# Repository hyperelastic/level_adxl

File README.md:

# level_adxl
Electronic level using the adxl325 accelerometer

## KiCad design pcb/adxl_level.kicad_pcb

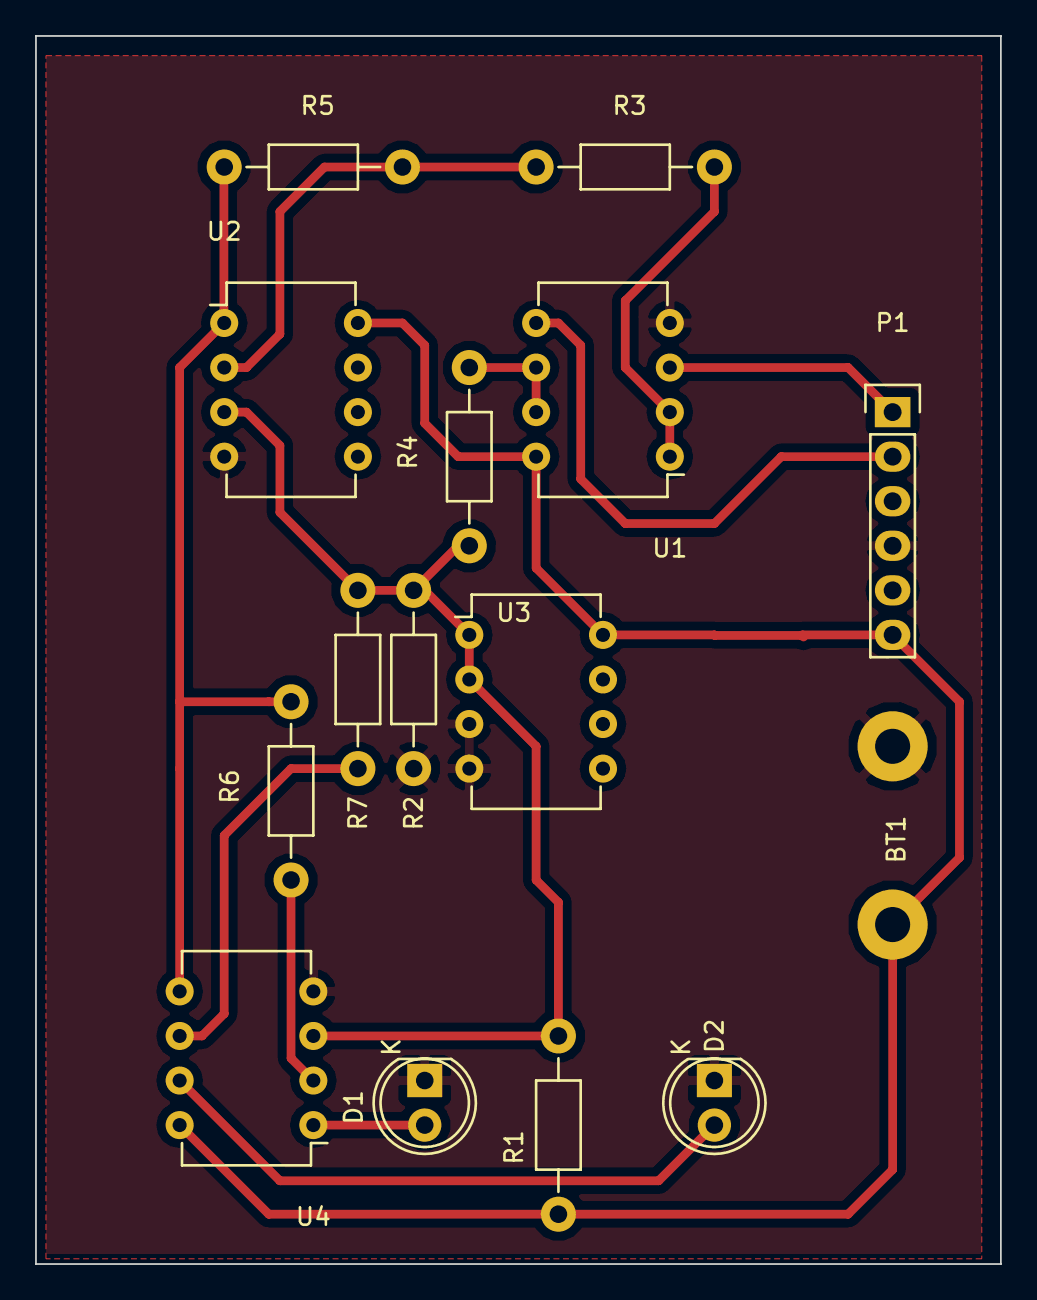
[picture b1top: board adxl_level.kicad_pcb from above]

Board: 2 copper layers, 55.0 x 70.0 mm, 15 parts (0 on the bottom side), 13 nets.

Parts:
BT1: Battery 9V; WireConnection_2.00mmDrill
D1, D2: LED; LED-5MM
P1: CONN_01X06; Pin_Header_Straight_1x06
R1, R2, R5: 33k; Resistor_Horizontal_RM10mm
R3, R4: 330; Resistor_Horizontal_RM10mm
R6, R7: 220; Resistor_Horizontal_RM10mm
U1, U2, U3, U4: LM358N; DIP-8_W7.62mm

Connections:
+9V: BT1.1, P1.6, R1.2, U1.8, U2.8, U3.8, U4.8
/Xout: P1.1, U1.3
/Yout: P1.2, U1.5
GND: BT1.2, D1.1, D2.1, P1.4, R2.1, U1.4, U2.4, U3.3, U3.4, U4.4
unnamed: D1.2, U4.1
unnamed: D2.2, U4.7
unnamed: R1.1, R2.2, R4.1, R7.2, U2.3, U3.1, U3.2, U4.3
unnamed: R3.1, R5.2, U2.2
unnamed: R3.2, U1.1, U1.2
unnamed: R4.2, U1.6, U1.7
unnamed: R5.1, R6.2, U2.1, U4.5
unnamed: R6.1, U4.2
unnamed: R7.1, U4.6

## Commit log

2016-06-21 Git enabled
2016-06-21 Renamed files.
2016-06-21 Moved .gitignore
2016-06-22 PCB designed
2016-06-22 Improved README
2016-06-29 Fixed too narrow connections
2016-07-26 Optimize connection and traces
